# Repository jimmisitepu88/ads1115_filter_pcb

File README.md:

# ads1115_filter_pcb
circuit filter ads1115, adc 16bit, 
for stable output
thanks

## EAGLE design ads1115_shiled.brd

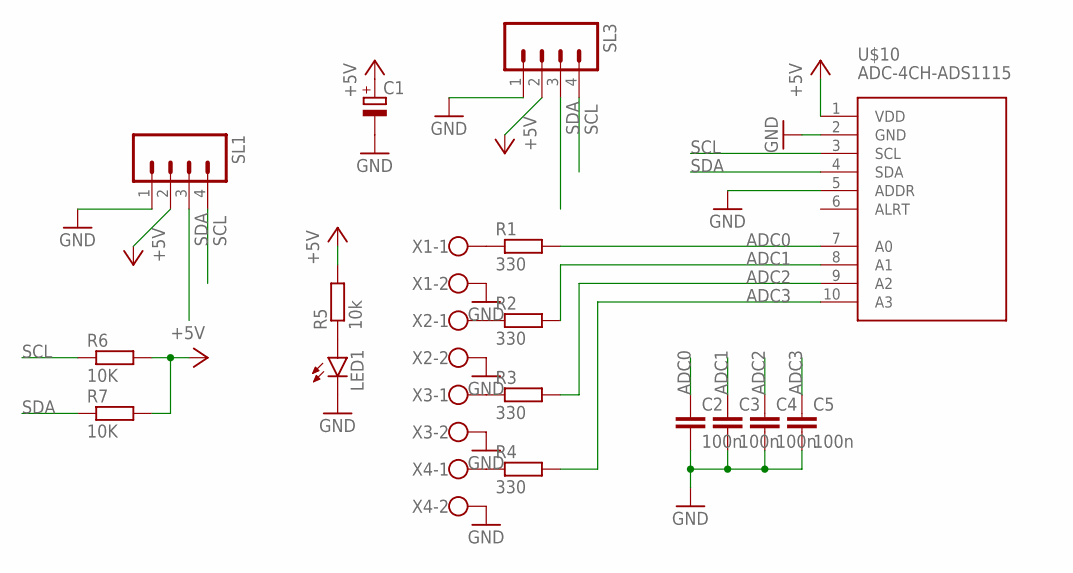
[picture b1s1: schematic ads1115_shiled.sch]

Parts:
C1: CPOL-EUE5-8.5; E5-8,5
C2, C3, C4, C5: 100n; C1206
LED1: LED3MM
R1, R2, R3, R4: 330; M1206
R5: 10k; M1206
R6, R7: 10K; M1206
SL1, SL3: M04; 04P
U$10: ADC-4CH-ADS1115
X1, X2, X3, X4: W237-102

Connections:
+5V: C1.+, R5.2, R6.2, R7.2, SL1.2, SL3.2, U$10.1 (VDD)
ADC0: C2.1, R1.2, U$10.7 (A0)
ADC1: C3.1, R2.2, U$10.8 (A1)
ADC2: C4.1, R3.2, U$10.9 (A2)
ADC3: C5.1, R4.2, U$10.10 (A3)
GND: C1.-, C2.2, C3.2, C4.2, C5.2, LED1.K (C), SL1.1, SL3.1, U$10.2 (GND), U$10.5 (ADDR), X1.2, X2.2, X3.2, X4.2
unnamed: R1.1, X1.1
unnamed: R2.1, X2.1
unnamed: R3.1, X3.1
unnamed: R4.1, X4.1
unnamed: LED1.A, R5.1
SCL: R6.1, SL1.4, SL3.4, U$10.3 (SCL)
SDA: R7.1, SL1.3, SL3.3, U$10.4 (SDA)

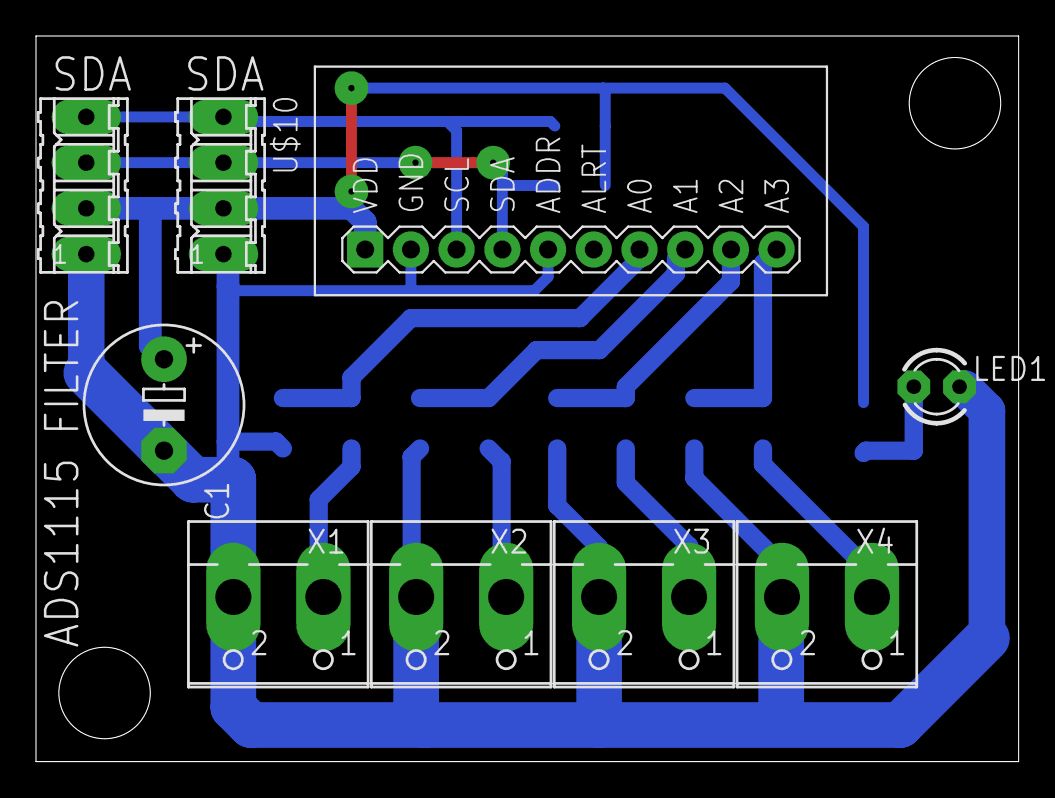
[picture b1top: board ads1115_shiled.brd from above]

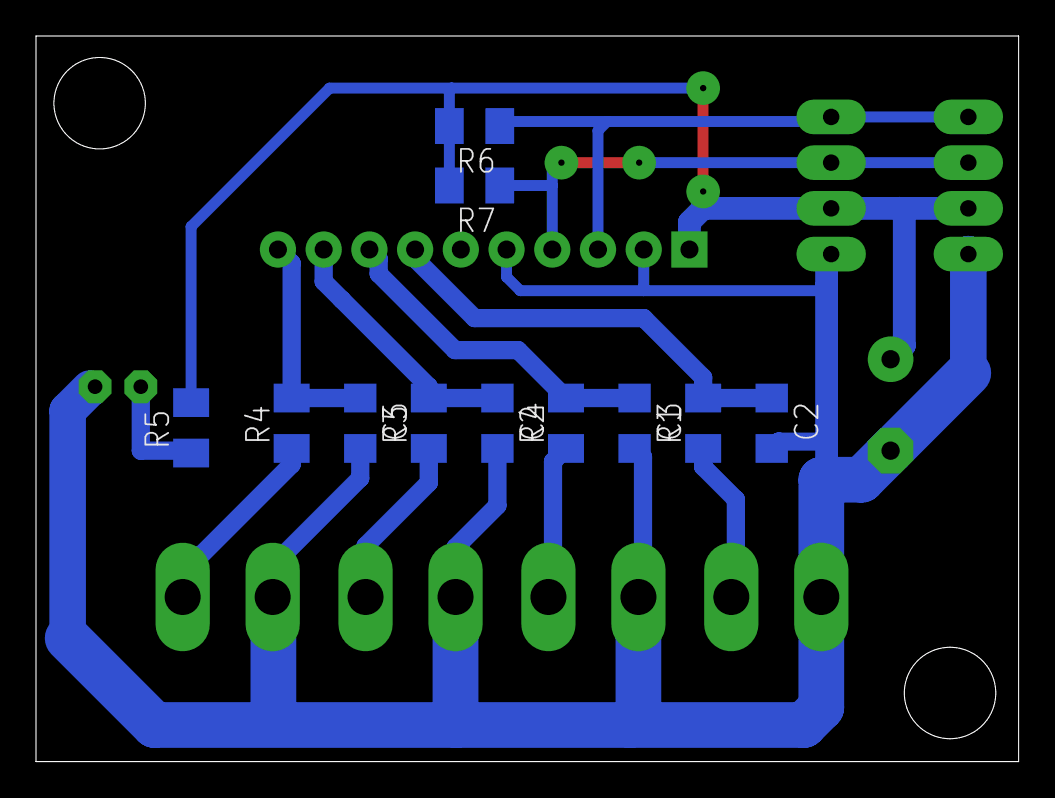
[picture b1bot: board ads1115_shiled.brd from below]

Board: 2 copper layers, 54.6 x 40.3 mm, 20 parts (11 on the bottom side), 13 nets.

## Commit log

2019-05-06 Add files via upload
    add circuit ads1115 filter

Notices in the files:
parts and their libraries:
diy-modules: Released under the Creative Commons Attribution 4.0 International License: http://creativecommons.org/licenses/by/4.0
